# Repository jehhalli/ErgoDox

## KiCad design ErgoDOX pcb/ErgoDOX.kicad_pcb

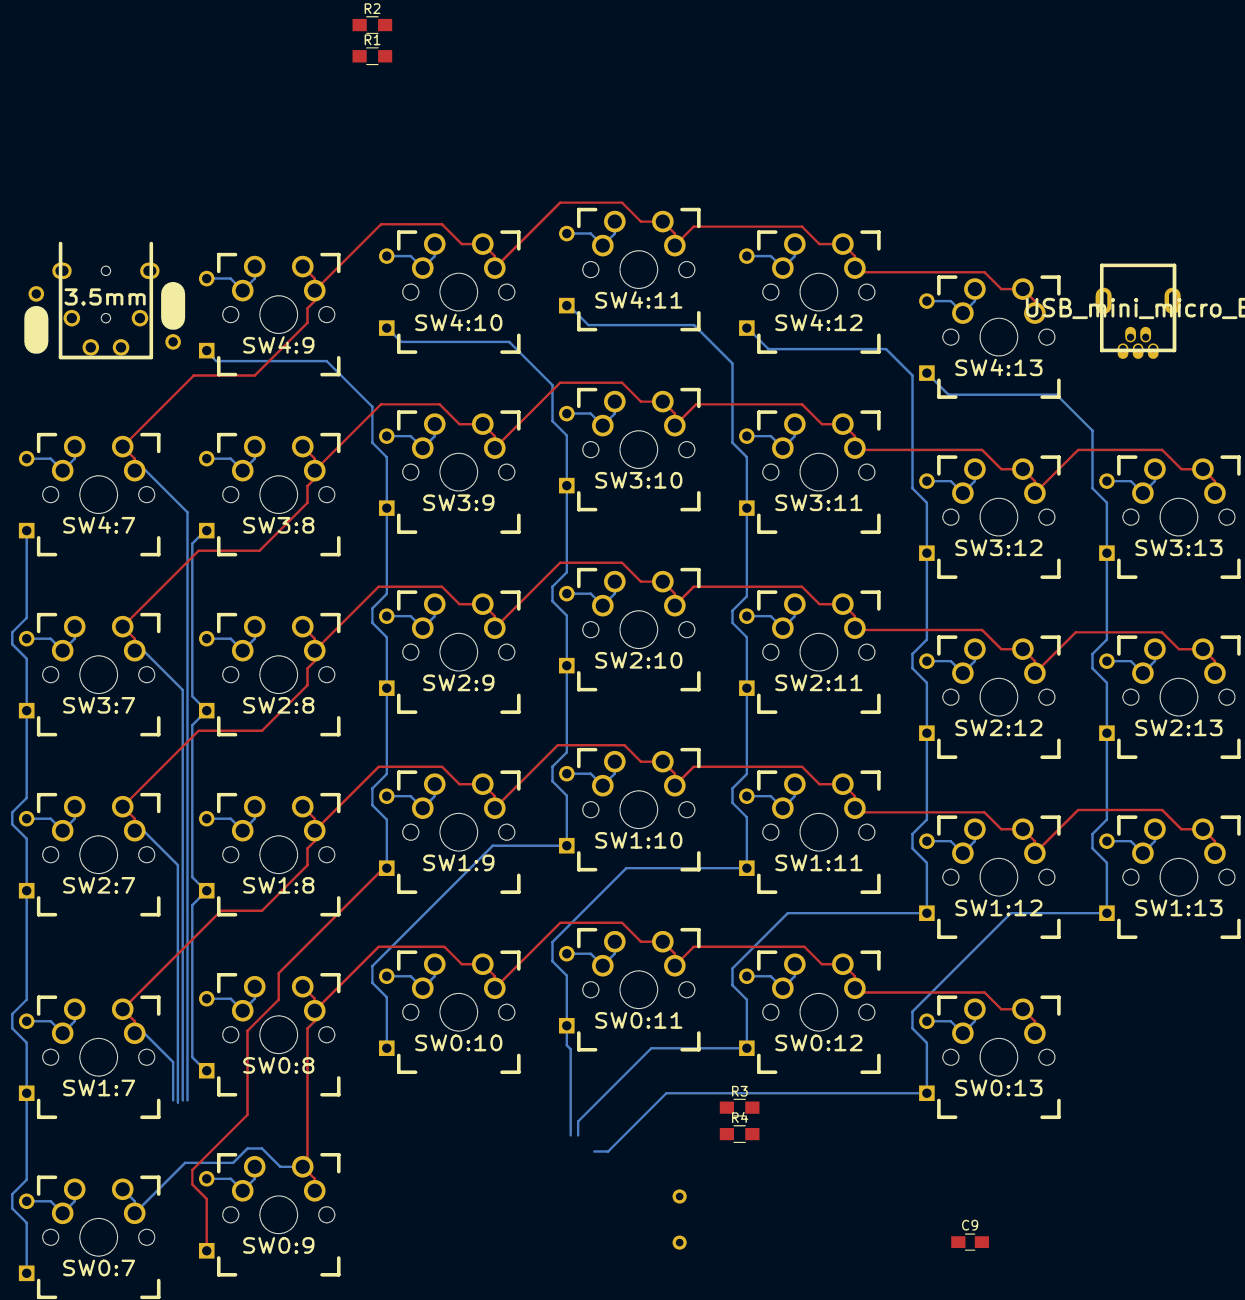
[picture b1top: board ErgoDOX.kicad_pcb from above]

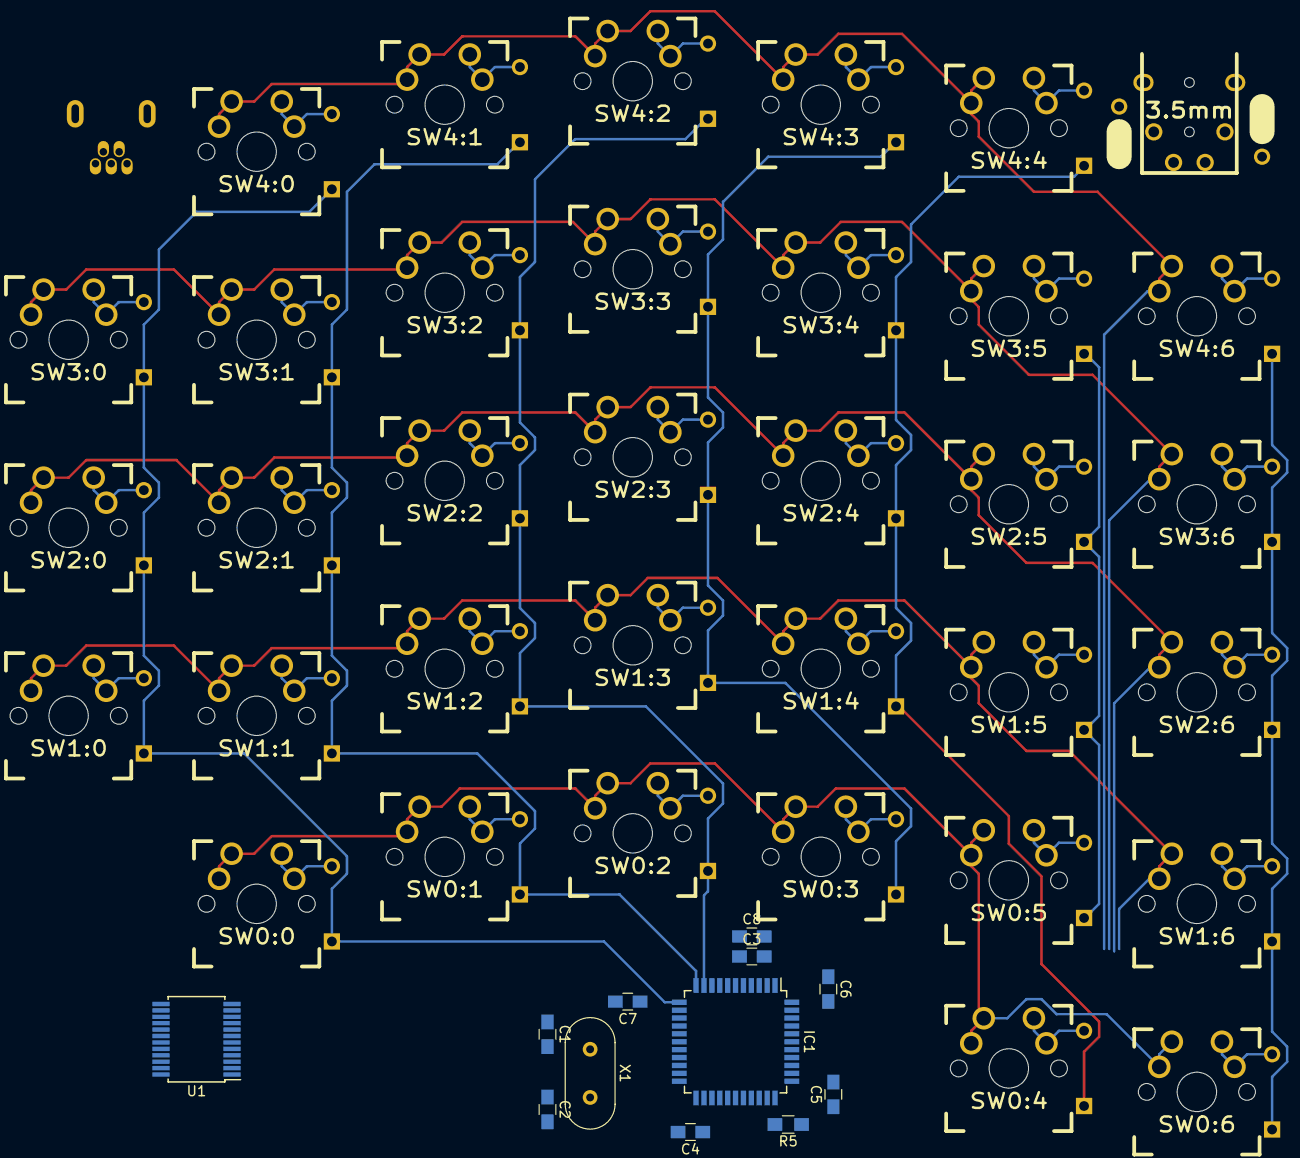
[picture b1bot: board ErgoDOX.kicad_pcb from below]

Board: 2 copper layers, 55 parts (14 on the bottom side), 60 nets.

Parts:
C1, C2: 32pF; C_0805_HandSoldering
C3, C4, C5, C6, C7, C8, C9: 1uF; C_0805_HandSoldering
IC1: ATMEGA32U4; TQFP-44_10x10mm_Pitch0.8mm
J1, J4: JMP; 100PITCH1X3
J2: USB_mini_micro_B; USBMINI
J3: 3.5mm; 4pin35mmAudio
R1, R2: 2.2kΩ; R_0805_HandSoldering
R3, R4: 22; R_0805_HandSoldering
R5: 1k; R_0805_HandSoldering
SW0:7: SW0:6; MX_FLIP_DIODE_mod
SW0:8: SW0:5; MX_FLIP_DIODE_mod
SW0:9: SW0:4; MX_FLIP_DIODE_mod
SW0:10: SW0:3; MX_FLIP_DIODE_mod
SW0:11: SW0:2; MX_FLIP_DIODE_mod
SW0:12: SW0:1; MX_FLIP_DIODE_mod
SW0:13: SW0:0; MX_FLIP_DIODE_mod
SW1:7: SW1:6; MX_FLIP_DIODE_mod
SW1:8: SW1:5; MX_FLIP_DIODE_mod
SW1:9: SW1:4; MX_FLIP_DIODE_mod
SW1:10: SW1:3; MX_FLIP_DIODE_mod
SW1:11: SW1:2; MX_FLIP_DIODE_mod
SW1:12: SW1:1; MX_FLIP_DIODE_mod
SW1:13: SW1:0; MX_FLIP_DIODE_mod
SW2:7: SW2:6; MX_FLIP_DIODE_mod
SW2:8: SW2:5; MX_FLIP_DIODE_mod
SW2:9: SW2:4; MX_FLIP_DIODE_mod
SW2:10: SW2:3; MX_FLIP_DIODE_mod
SW2:11: SW2:2; MX_FLIP_DIODE_mod
SW2:12: SW2:1; MX_FLIP_DIODE_mod
SW2:13: SW2:0; MX_FLIP_DIODE_mod
SW3:7: SW3:6; MX_FLIP_DIODE_mod
SW3:8: SW3:5; MX_FLIP_DIODE_mod
SW3:9: SW3:4; MX_FLIP_DIODE_mod
SW3:10: SW3:3; MX_FLIP_DIODE_mod
SW3:11: SW3:2; MX_FLIP_DIODE_mod
SW3:12: SW3:1; MX_FLIP_DIODE_mod
SW3:13: SW3:0; MX_FLIP_DIODE_mod
SW4:7: SW4:6; MX_FLIP_DIODE_mod
SW4:9: SW4:4; MX_FLIP_DIODE_mod
SW4:10: SW4:3; MX_FLIP_DIODE_mod
SW4:11: SW4:2; MX_FLIP_DIODE_mod
SW4:12: SW4:1; MX_FLIP_DIODE_mod
SW4:13: SW4:0; MX_FLIP_DIODE_mod
U1: MCP23018-SSOP; SSOP-24_5.3x8.2mm_Pitch0.65mm
X1: XTAL; Crystal_HC49-U_Vertical

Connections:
/COL0: IC1.12, SW0:13.4, SW1:13.4, SW2:13.4, SW3:13.4, SW4:13.4
/COL1: IC1.11, SW0:12.4, SW1:12.4, SW2:12.4, SW3:12.4, SW4:12.4
/COL4: IC1.32, SW0:9.4, SW1:9.4, SW2:9.4, SW3:9.4, SW4:9.4
/COL5: IC1.40, SW0:8.4, SW1:8.4, SW2:8.4, SW3:8.4
/COL6: IC1.30, SW0:7.4, SW1:7.4, SW2:7.4, SW3:7.4, SW4:7.4
/COL10: IC1.41, SW0:10.4, SW1:10.4, SW2:10.4, SW3:10.4, SW4:10.4
/COL11: IC1.10, SW0:11.4, SW1:11.4, SW2:11.4, SW3:11.4, SW4:11.4
/ROW0: IC1.31, SW0:7.1, SW0:8.1, SW0:9.1, SW0:10.1, SW0:11.1, SW0:12.1, SW0:13.1
/ROW1: IC1.36, SW1:7.1, SW1:8.1, SW1:9.1, SW1:10.1, SW1:11.1, SW1:12.1, SW1:13.1
/ROW2: IC1.37, SW2:7.1, SW2:8.1, SW2:9.1, SW2:10.1, SW2:11.1, SW2:12.1, SW2:13.1
/ROW3: IC1.38, SW3:7.1, SW3:8.1, SW3:9.1, SW3:10.1, SW3:11.1, SW3:12.1, SW3:13.1
/ROW4: IC1.39, SW4:7.1, SW4:9.1, SW4:10.1, SW4:11.1, SW4:12.1, SW4:13.1
/SCLM: IC1.18, J3.3, J3.5, R2.2, U1.11
/SDAM: IC1.19, J3.2, J3.6, R1.2, U1.12
GND: C1.2, C2.2, C3.2, C4.2, C5.2, C6.2, C7.2, C8.2, C9.2, IC1.5, IC1.15, IC1.23, IC1.35, IC1.43, J1.3, J2.5, J2.6, J4.3, R5.1, U1.1
unnamed: C1.1, IC1.16, X1.1
unnamed: C2.1, IC1.17, X1.2
unnamed: C3.1, IC1.6
unnamed: IC1.3, R3.1
unnamed: IC1.4, R4.1
unnamed: IC1.33, R5.2
unnamed: J1.2, J3.1
unnamed: J2.2, R3.2
unnamed: J2.3, R4.2
unnamed: J3.4, J4.2
unnamed: SW0:7.2, SW0:7.3
unnamed: SW0:8.2, SW0:8.3
unnamed: SW0:9.2, SW0:9.3
unnamed: SW0:10.2, SW0:10.3
unnamed: SW0:11.2, SW0:11.3
unnamed: SW0:12.2, SW0:12.3
unnamed: SW0:13.2, SW0:13.3
unnamed: SW1:7.2, SW1:7.3
unnamed: SW1:8.2, SW1:8.3
unnamed: SW1:9.2, SW1:9.3
unnamed: SW1:10.2, SW1:10.3
unnamed: SW1:11.2, SW1:11.3
unnamed: SW1:12.2, SW1:12.3
unnamed: SW1:13.2, SW1:13.3
unnamed: SW2:7.2, SW2:7.3
unnamed: SW2:8.2, SW2:8.3
unnamed: SW2:9.2, SW2:9.3
unnamed: SW2:10.2, SW2:10.3
unnamed: SW2:11.2, SW2:11.3
unnamed: SW2:12.2, SW2:12.3
unnamed: SW2:13.2, SW2:13.3
unnamed: SW3:7.2, SW3:7.3
unnamed: SW3:8.2, SW3:8.3
unnamed: SW3:9.2, SW3:9.3
unnamed: SW3:10.2, SW3:10.3
unnamed: SW3:11.2, SW3:11.3
unnamed: SW3:12.2, SW3:12.3
unnamed: SW3:13.2, SW3:13.3
unnamed: SW4:7.2, SW4:7.3
unnamed: SW4:9.2, SW4:9.3
unnamed: SW4:10.2, SW4:10.3
unnamed: SW4:11.2, SW4:11.3
unnamed: SW4:12.2, SW4:12.3
unnamed: SW4:13.2, SW4:13.3
VCC: C4.1, C5.1, C6.1, C7.1, C8.1, C9.1, IC1.2, IC1.7, IC1.14, IC1.24, IC1.34, IC1.44, J1.1, J2.1, J4.1, R1.1, R2.1, U1.10

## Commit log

2017-05-19 Long overdue update to the board.
